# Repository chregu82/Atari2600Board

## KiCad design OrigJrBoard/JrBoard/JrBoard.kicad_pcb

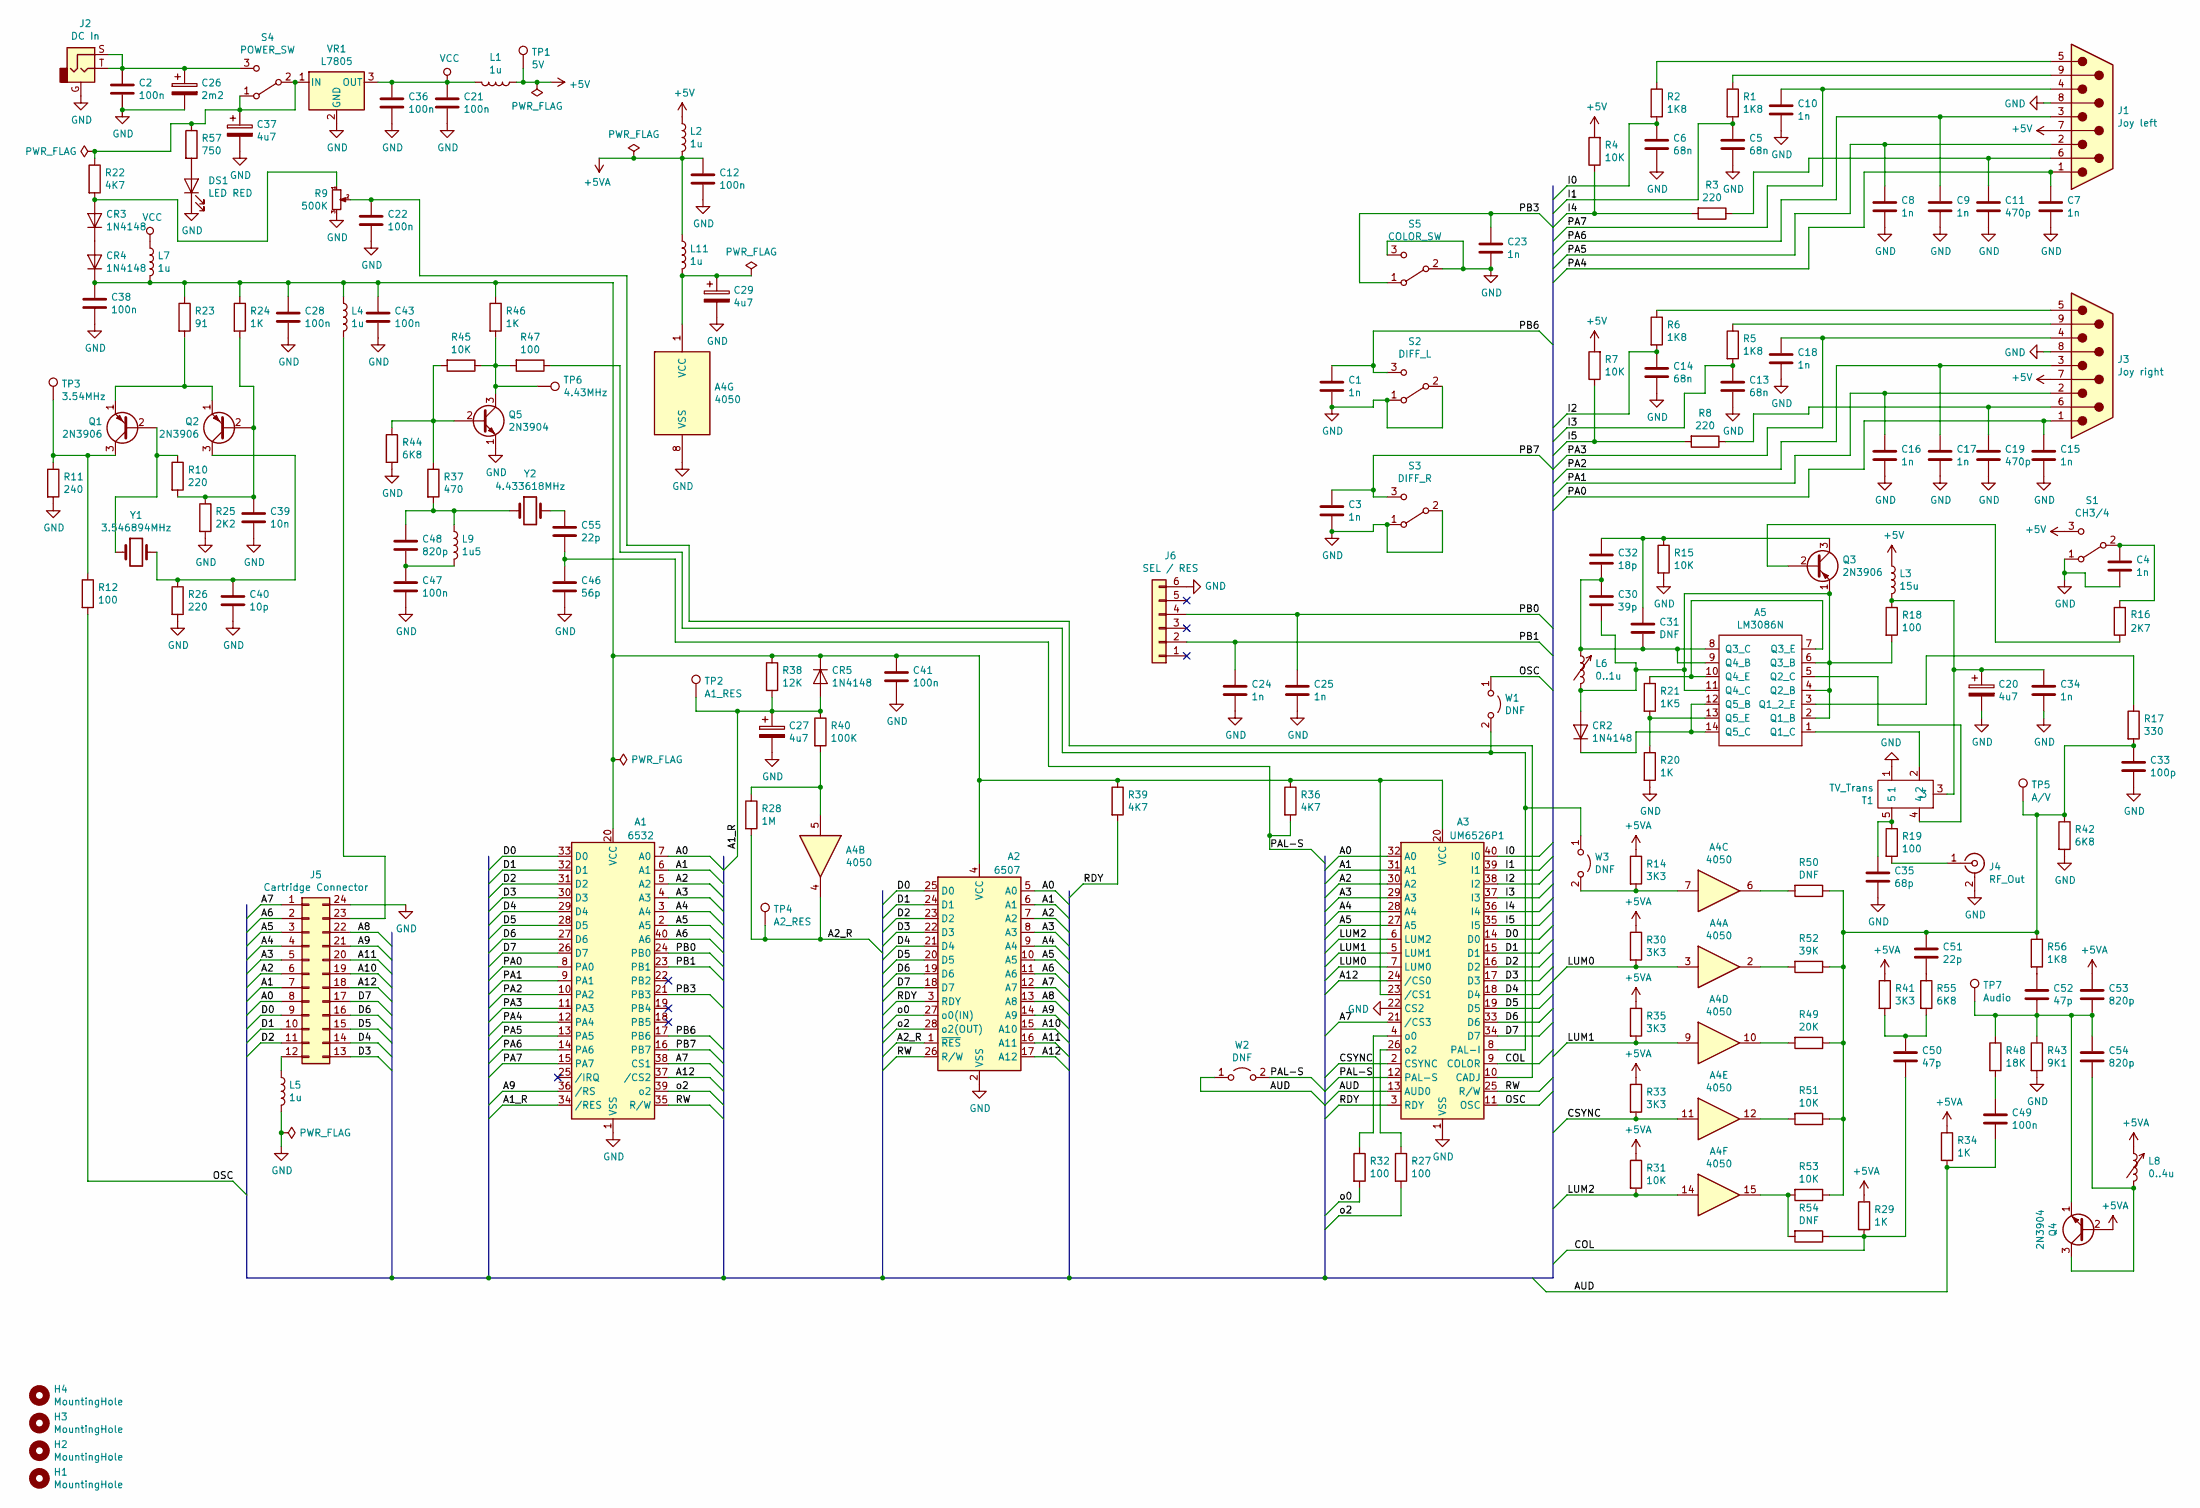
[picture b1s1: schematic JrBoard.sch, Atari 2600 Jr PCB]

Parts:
A1: 6532; DIP-40_W15.24mm
A2: 6507; DIP-28_W15.24mm
A3: UM6526P1; DIP-40_W15.24mm
A4: 4050; DIP-16_W7.62mm
A5: LM3086N; DIP-14_W7.62mm
C1, C3, C4, C7, C8, C9, C10, C15, C16, C17, C18, C23, C24, C25, C34: 1n; C_leg_small
C2, C12, C21, C22, C28, C36, C38, C41, C43, C47, C49: 100n; C_leg_small
C5, C6, C13, C14: 68n; C_oval_big
C11, C19: 470p; C_leg_small
C20, C27, C29, C37: 4u7; CP_small
C26: 2m2; CP_big
C30: 39p; C_oval_small
C31: DNF; C_oval_small
C32: 18p; C_4hole
C33: 100p; C_leg_small
C35: 68p; C_leg_small
C39: 10n; C_leg_small
C40: 10p; C_leg_small
C46: 56p; C_leg_small
C48, C53, C54: 820p; C_leg_big
C50, C52: 47p; C_leg_small
C51, C55: 22p; C_leg_small
CR2: 1N4148; Diode_short
CR3, CR4, CR5: 1N4148; Diode
DS1: LED RED; LED_D5.0mm_Clear
H1, H2, H4: MountingHole; HoleEdge
H3: MountingHole; HoleTop
J1: Joy left; Joystick_conn
J2: DC In; DC_IN
J3: Joy right; Joystick_conn
J4: RF_Out
J5: Cartridge Connector; Cartridge
J6: SEL / RES; Button_conn
L1, L2, L4, L5, L7, L11: 1u; L_small
L3: 15u; L_big
L6: 0..1u; L_var_2pin
L8: 0..4u; L_var_5pin
L9: 1u5; L_big
Q1, Q2, Q3: 2N3906; TR_TO92
Q4, Q5: 2N3904; TR_TO92
R1, R2, R5, R6, R56: 1K8; R0.5Inch
R3, R8, R10, R26: 220; R0.5Inch
R4, R7, R31, R45, R51, R53: 10K; R0.5Inch
R9: 500K; R_Var
R11: 240; R0.5Inch
R12, R19, R27, R32, R47: 100; R0.5Inch
R14, R30, R33, R35, R41: 3K3; R0.5Inch
R15: 10K; R_small
R16: 2K7; R_small
R17: 330; R_small
R18: 100; R_small
R20: 1K; R_small
R21: 1K5; R_small
R22, R36, R39: 4K7; R0.5Inch
R23: 91; R0.5Inch
R24, R29, R34, R46: 1K; R0.5Inch
R25: 2K2; R0.5Inch
R28: 1M; R0.5Inch
R37: 470; R0.5Inch
R38: 12K; R0.5Inch
R40: 100K; R0.5Inch
R42, R44, R55: 6K8; R0.5Inch
R43: 9K1; R0.5Inch
R48: 18K; R0.5Inch
R49: 20K; R0.5Inch
R50, R54: DNF; R0.5Inch
R52: 39K; R0.5Inch
R57: 750; R0.5Inch
S1: CH3/4; Switch_rear
S2: DIFF_L; Switch_rear
S3: DIFF_R; Switch_rear
S4: POWER_SW; Switch_top
S5: COLOR_SW; Switch_top
T1: TV_Trans; Atari_TV_Trans
TP1: 5V; TestPoint_THTPad_D2.0mm_Drill1.0mm
TP2: A1_RES; TestPoint_THTPad_D2.0mm_Drill1.0mm
TP3: 3.54MHz; TestPoint_THTPad_D2.0mm_Drill1.0mm
TP4: A2_RES; TestPoint_THTPad_D2.0mm_Drill1.0mm
TP5: A/V; TestPoint_THTPad_D2.0mm_Drill1.0mm
TP6: 4.43MHz; TestPoint_THTPad_D2.0mm_Drill1.0mm
TP7: Audio; TestPoint_THTPad_D2.0mm_Drill1.0mm
VR1: L7805; TO-220-3_Horizontal_TabDown
W1, W2, W3: DNF; Wire
Y1: 3.546894MHz; Crystal_HC18-U_Vertical
Y2: 4.433618MHz; Crystal_HC18-U_Vertical

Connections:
+5V: J1.7, J3.7, L1.1, L2.1, L3.1, R4.2, R7.2, S1.3 (C), TP1.1
+5VA: C12.1, C53.1, L2.2, L8.1, L11.1, Q4.2 (B), R14.1, R29.1, R30.1, R31.1, R33.1, R34.1, R35.1, R41.1
/A0: A1.7 (A0), A2.5 (A0), A3.32 (A0), J5.8
/A1: A1.6 (A1), A2.6 (A1), A3.31 (A1), J5.7
/A1_R: A1.34 (/RES), C27.1, CR5.2 (A), R38.2, R40.1, TP2.1
/A2: A1.5 (A2), A2.7 (A2), A3.30 (A2), J5.6
/A2_R: A2.1 (~RES), A4.4, R28.2, TP4.1
/A3: A1.4 (A3), A2.8 (A3), A3.29 (A3), J5.5
/A4: A1.3 (A4), A2.9 (A4), A3.28 (A4), J5.4
/A5: A1.2 (A5), A2.10 (A5), A3.27 (A5), J5.3
/A6: A1.40 (A6), A2.11 (A6), J5.2
/A7: A1.38 (CS1), A2.12 (A7), A3.21 (/CS3), J5.1
/A8: A2.13 (A8), J5.22
/A9: A1.36 (/RS), A2.14 (A9), J5.21
/A10: A2.15 (A10), J5.19
/A11: A2.16 (A11), J5.20
/A12: A1.37 (/CS2), A2.17 (A12), A3.24 (/CS0), J5.18
/AUD: A3.13 (AUD0), C49.2, R34.2, W2.1 (A)
/COL: A3.9 (COLOR), C50.2, R29.2, R54.1
/CSYNC: A3.2 (CSYNC), A4.11, R33.2
/D0: A1.33 (D0), A2.25 (D0), A3.14 (D0), J5.9
/D1: A1.32 (D1), A2.24 (D1), A3.15 (D1), J5.10
/D2: A1.31 (D2), A2.23 (D2), A3.16 (D2), J5.11
/D3: A1.30 (D3), A2.22 (D3), A3.17 (D3), J5.13
/D4: A1.29 (D4), A2.21 (D4), A3.18 (D4), J5.14
/D5: A1.28 (D5), A2.20 (D5), A3.19 (D5), J5.15
/D6: A1.27 (D6), A2.19 (D6), A3.33 (D6), J5.16
/D7: A1.26 (D7), A2.18 (D7), A3.34 (D7), J5.17
/I0: A3.40 (I0), C6.1, R2.2
/I1: A3.39 (I1), C5.1, R1.2
/I2: A3.38 (I2), C14.1, R6.2
/I3: A3.37 (I3), C13.1, R5.2
/I4: A3.36 (I4), R3.2, R4.1
/I5: A3.35 (I5), R7.1, R8.2
/LUM0: A3.7 (LUM0), A4.3, R30.2
/LUM1: A3.5 (LUM1), A4.9, R35.2
/LUM2: A3.6 (LUM2), A4.14, R31.2
/OSC: A3.11 (OSC), R12.2, W1.1 (A)
/PA0: A1.8 (PA0), C15.1, J3.1
/PA1: A1.9 (PA1), C16.1, J3.2
/PA2: A1.10 (PA2), C17.1, J3.3
/PA3: A1.11 (PA3), C18.1, J3.4
/PA4: A1.12 (PA4), C7.1, J1.1
/PA5: A1.13 (PA5), C8.1, J1.2
/PA6: A1.14 (PA6), C9.1, J1.3
/PA7: A1.15 (PA7), C10.1, J1.4
/PAL-S: A3.12 (PAL-S), C46.1, C55.2, R36.2, W2.2 (B)
/PB0: A1.24 (PB0), C25.1, J6.4
/PB1: A1.23 (PB1), C24.1, J6.2
/PB3: A1.21 (PB3), C23.1, S5.1 (A)
/PB6: A1.17 (PB6), C1.1, S2.3 (C)
/PB7: A1.16 (PB7), C3.1, S3.3 (C)
/RDY: A2.3 (RDY), A3.3 (RDY), R39.2
/RW: A1.35 (R/W), A2.26 (R/W), A3.25 (R/W)
/o0: A2.27 (o0(IN)), R32.2
/o2: A1.39 (o2), A2.28 (o2(OUT)), R27.2
GND: A1.1 (VSS), A2.2 (VSS), A3.1 (VSS), A3.22 (CS2), A4.8 (VSS), C1.2, C2.2, C3.2, C4.2, C5.2, C6.2, C7.2, C8.2, C9.2, C10.2, C11.2, C12.2, C13.2, C14.2, C15.2, C16.2, C17.2, C18.2, C19.2, C20.2, C21.2, C22.2, C23.2, C24.2, C25.2, C26.2, C27.2, C28.2, C29.2, C33.2, C34.2, C35.2, C36.2, C37.2, C38.2, C39.2, C40.2, C41.2, C43.2, C46.2, C47.2, DS1.1 (K), J1.8, J2.G, J3.8, J4.2 (Ext), J5.24, J6.6, L5.2, Q5.1 (E), R9.3, R11.2, R15.2, R20.2, R25.2, R26.2, R42.2, R43.2, R44.2, S1.1 (A), S2.1 (A), S2.2 (B), S3.1 (A), S3.2 (B), S5.2 (B), S5.3 (C), T1.1, VR1.2 (GND)
unnamed: A1.20 (VCC), A2.4 (VCC), A3.20 (VCC), A3.23 (/CS1), C28.1, C38.1, C41.1, C43.1, CR4.1 (K), CR5.1 (K), L4.1, L7.2, R23.1, R24.1, R36.1, R38.1, R39.1, R46.1
unnamed: A3.4 (o0), R32.1
unnamed: A3.8 (PAL-I), R47.1, W1.2 (B), W3.1 (A)
unnamed: A3.10 (CADJ), C22.1, R9.2
unnamed: A3.26 (o2), R27.1
unnamed: A4.1 (VCC), C29.1, L11.2
unnamed: A4.2, R52.2
unnamed: A4.5, R28.1, R40.2
unnamed: A4.6, R50.2
unnamed: A4.7, R14.2, W3.2 (B)
unnamed: A4.10, R49.2
unnamed: A4.12, R51.2
unnamed: A4.15, R53.2, R54.2
unnamed: A5.1 (Q1_C), T1.2
unnamed: A5.3 (Q1_2_E), R17.1
unnamed: A5.5 (Q2_C), T1.4
unnamed: A5.8 (Q3_C), A5.9 (Q4_B), C30.1, C31.2, C32.2, L6.1
unnamed: A5.7 (Q3_E), A5.10 (Q4_E), R21.1
unnamed: A5.2 (Q1_B), A5.4 (Q2_B), A5.6 (Q3_B), A5.11 (Q4_C), C30.2, CR2.2 (A), L6.2, Q3.1 (E), R18.2
unnamed: A5.12 (Q5_B), A5.14 (Q5_C), CR2.1 (K)
unnamed: A5.13 (Q5_E), R20.1, R21.2
unnamed: C2.1, C26.1, J2.S, J2.T, S4.3 (C)
unnamed: C4.1, R16.2, S1.2 (B)
unnamed: C11.1, J1.6, R3.1
unnamed: C19.1, J3.6, R8.1
unnamed: C20.1, C34.1, L3.2, R18.1, T1.3
unnamed: C31.1, C32.1, Q3.3 (C), R15.1
unnamed: C33.1, C51.1, R17.2, R42.1, R49.1, R50.1, R51.1, R52.1, R53.1, R56.1, TP5.1
unnamed: C35.1, R19.1, T1.5
unnamed: C37.1, R22.1, R57.1, S4.1 (A), S4.2 (B), VR1.1 (IN)
unnamed: C39.1, Q2.2 (B), R10.2, R24.2, R25.1
unnamed: C40.1, Q2.3 (C), R26.1, Y1.2
unnamed: C47.1, C48.2, L9.2
unnamed: C48.1, L9.1, R37.2, Y2.1
unnamed: C49.1, R48.2
unnamed: C50.1, R41.2, R55.2
unnamed: C51.2, R55.1
unnamed: C52.1, R56.2
unnamed: C52.2, C53.2, C54.1, Q4.1 (E), R43.1, R48.1, TP7.1
unnamed: C54.2, L8.2, Q4.3 (C)
unnamed: C55.1, Y2.2
unnamed: CR3.1 (K), CR4.2 (A)
unnamed: CR3.2 (A), R9.1, R22.2
unnamed: DS1.2 (A), R57.2
unnamed: J1.5, R2.1
unnamed: J1.9, R1.1
unnamed: J3.5, R6.1
unnamed: J3.9, R5.1
unnamed: J4.1 (In), R19.2
unnamed: J5.12, L5.1
unnamed: J5.23, L4.2
unnamed: Q1.1 (E), Q2.1 (E), R23.2
unnamed: Q1.2 (B), R10.1, Y1.1
unnamed: Q1.3 (C), R11.1, R12.1, TP3.1
unnamed: Q3.2 (B), R16.1
unnamed: Q5.2 (B), R37.1, R44.1, R45.2
unnamed: Q5.3 (C), R45.1, R46.2, R47.2, TP6.1
VCC: C21.1, C36.1, L1.2, L7.1, VR1.3 (OUT)

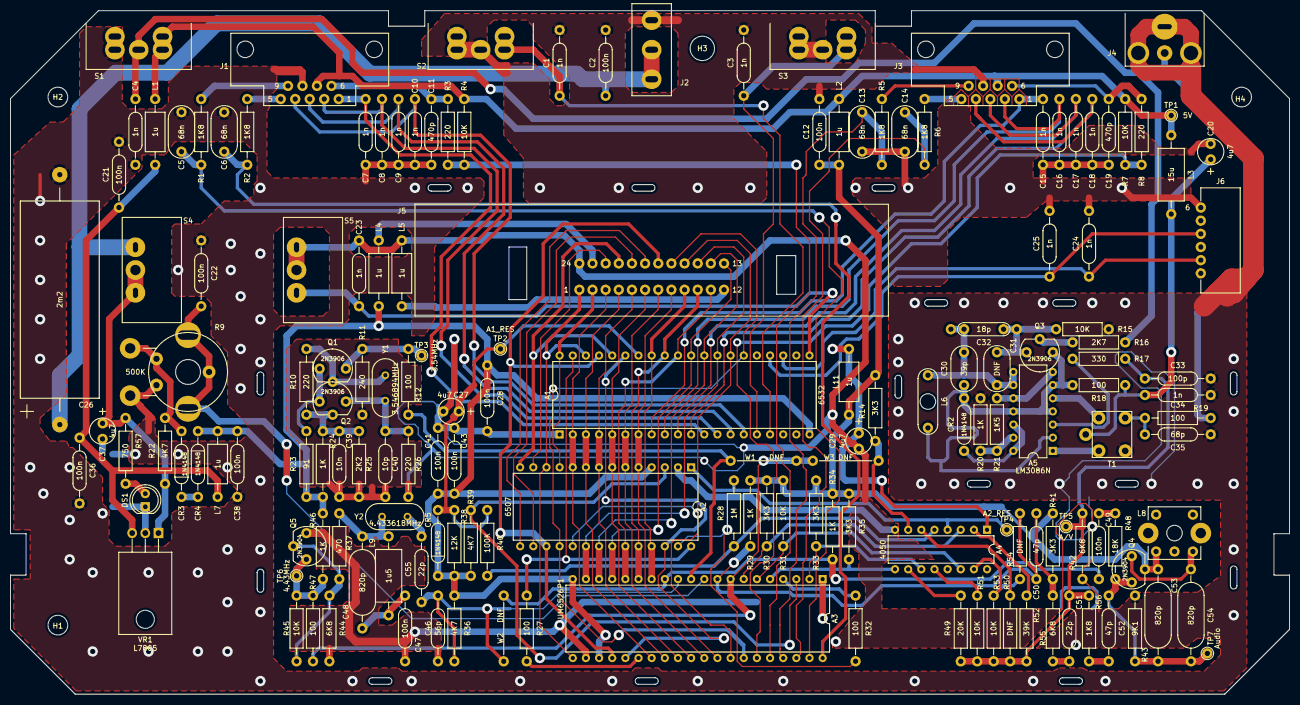
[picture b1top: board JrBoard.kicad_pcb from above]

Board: 2 copper layers, 247.0 x 132.0 mm, 162 parts (0 on the bottom side), 115 nets.

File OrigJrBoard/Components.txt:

Atari Jr. Board PAL C021503 REV F

Name            Description               Value
A1              RIOT                      UM6532
A2              CPU                       R6507-15
A3              TIA                       UM6526
A4              Hex Buffer                CD4050BCN
A5              5x NPN Transistor         LM3086N
C1              Capacitor                 1nF
C2              Capacitor                 100nF
C3              Capacitor                 1nF
C4              Capacitor                 1nF
C5              Capacitor                 68nF
C6              Capacitor                 68nF
C7              Capacitor                 1nF
C8              Capacitor                 1nF
C9              Capacitor                 1nF
C10             Capacitor                 1nF
C11             Capacitor                 470pF
C12             Capacitor                 100nF
C13             Capacitor                 68nF
C14             Capacitor                 68nF
C15             Capacitor                 1nF
C16             Capacitor                 1nF
C17             Capacitor                 1nF
C18             Capacitor                 1nF
C19             Capacitor                 470pF
C20             Electrolytic cap          4.7uF 35V
C21             Capacitor                 100nF
C22             Capacitor                 100nF
C23             Capacitor                 1nF
C24             Capacitor                 1nF
C25             Capacitor                 1nF
C26             Electrolytic cap          2200uF 16V
C27             Electrolytic cap          4.7uF 35V
C28             Capacitor                 100nF
C29             Electrolytic cap          4.7uF 35V
C30             Capacitor                 39pF
C31             empty
C32             Capacitor                 18pF
C33             Capacitor                 100pF
C34             Capacitor                 1nF
C35             Capacitor                 68pF
C36             Capacitor                 100nF
C37             Electrolytic cap          4.7uF 35V
C38             Capacitor                 100nF
C39             Capacitor                 10nF
C40             Capacitor                 10pF
C41             Capacitor                 100nF
C43             Capacitor                 100nF
C46             Capacitor                 56pF
C47             Capacitor                 100nF
C48             Styroflex cap             820pF
C49             Capacitor                 100nF
C50             Capacitor                 47pF
C51             Capacitor                 22pF
C52             Capacitor                 47pF
C53             Styroflex cap             820pF
C54             Styroflex cap             820pF
C55             Capacitor                 22pF
CR2             Diode                     1N4148
CR3             Diode                     1N4148
CR4             Diode                     1N4148
CR5             Diode                     1N4148
DS1             Power LED                 red
J1              Left Joystick Port        FOXCONN male SUBD9 port
J2              9V DC-In Port             Mono Audio Like female port
J3              Right Joystick Port       FOXCONN male SUBD9 port
J4              RF Connector              Cinch Type female
J5              Cartridge Connector       24pin 1.57mm card edge connector
J6              Select/Reset connector    6pin
L1              Inductance                1uH
L2              Inductance                1uH
L3              Inductance                15uH 10%
L4              Inductance                1uH
L5              Inductance                1uH
L6              Variable Inductance       0.7uH
L7              Inductance                1uH
L8              Variable Inductance       2.6 uH
L9              Inductance                1.5uH
L11             Inductance                1uH
Q1              Transistor PNP            2N 3906
Q2              Transistor PNP            2N 3906
Q3              Transistor PNP            2N 3906
Q4              Transistor NPN            2N 3904
Q5              Transistor NPN            2N 3904
R1              Resistor                  1K8 5% 0.25W
R2              Resistor                  1K8 5% 0.25W
R3              Resistor                  220R 5% 0.25W
R4              Resistor                  10K 5% 0.25W
R5              Resistor                  1K8 5% 0.25W
R6              Resistor                  1K8 5% 0.25W
R7              Resistor                  10K 5% 0.25W
R8              Resistor                  220R 5% 0.25W
R9              Variable resistor         500K         
R10             Resistor                  220R 5% 0.25W
R11             Resistor                  240R 5% 0.25W
R12             Resistor                  100R 5% 0.25W
R14             Resistor                  3K3 5% 0.25W
R15             Resistor                  10K 5% 0.25W
R16             Resistor                  2K7 5% 0.25W
R17             Resistor                  330R 5% 0.25W
R18             Resistor                  100R 5% 0.25W
R19             Resistor                  100R 5% 0.25W
R20             Resistor                  1K 5% 0.25W
R21             Resistor                  1K5 5% 0.25W
R22             Resistor                  4K7 5% 0.25W
R23             Resistor                  91R 5% 0.25W
R24             Resistor                  1K 5% 0.25W
R25             Resistor                  2K2 5% 0.25W
R26             Resistor                  220R 5% 0.25W
R27             Resistor                  100R 5% 0.25W
R28             Resistor                  1M 5% 0.25W
R29             Resistor                  1K 5% 0.25W
R30             Resistor                  3K3 5% 0.25W
R31             Resistor                  10K 5% 0.25W
R32             Resistor                  100R 5% 0.25W
R33             Resistor                  3K3 5% 0.25W
R34             Resistor                  1K 5% 0.25W
R35             Resistor                  3K3 5% 0.25W
R36             Resistor                  4K7 5% 0.25W
R37             Resistor                  470R 5% 0.25W
R38             Resistor                  12K 5% 0.25W
R39             Resistor                  4K7 5% 0.25W
R40             Resistor                  100K 5% 0.25W
R41             Resistor                  3K3 5% 0.25W
R42             Resistor                  6K8 5% 0.25W
R43             Resistor                  9K1 5% 0.25W
R44             Resistor                  6K8 5% 0.25W
R45             Resistor                  10K 5% 0.25W
R46             Resistor                  1K 5% 0.25W
R47             Resistor                  100R 5% 0.25W
R48             Resistor                  18K 5% 0.25W
R49             Resistor                  20K 5% 0.25W
R50             empty
R51             Resistor                  10K 5% 0.25W
R52             Resistor                  39K 5% 0.25W
R53             Resistor                  10K 5% 0.25W
R54             empty
R55             Resistor                  6K8 5% 0.25W
R56             Resistor                  1K8 5% 0.25W
R57             Resistor                  750R 5% 0.25W
S1              Channel Switch            RS C019702-01
S2              Left Difficulty Switch    RS C019702-01
S3              Right Difficulty Switch   RS C019702-01
S4              Power switch              RS C020480-02
S5              Color switch              RS C020480-02
T1              Some strange 1 wire transformer
VR1             5V volatage regulator     LM340T5 7805
Y1              Quarz oscillator          3.546894MHz
Y2              Quarz oscillator          4.433618MHz

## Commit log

2020-12-07 Final parts list original board
2020-12-07 Corrections parts list
2020-12-09 Working on schematic
2020-12-13 Continued schematic
2020-12-14 finished schematic
2020-12-14 Footprints
2020-12-14 Started PCB
2020-12-15 PCB work
2020-12-18 PCB top mostly done
2020-12-20 Finished PCB
2020-12-20 Added Gerber files, going to production
2021-01-02 Trying to build a board with Composite and Pause Mod
2021-01-02 Schematic corrections
2021-01-05 Right footprints for diode
2021-01-05 Corrections after first production
2021-01-06 PCB corrections
2021-01-10 New gerber files
2021-01-26 Minor corrections
